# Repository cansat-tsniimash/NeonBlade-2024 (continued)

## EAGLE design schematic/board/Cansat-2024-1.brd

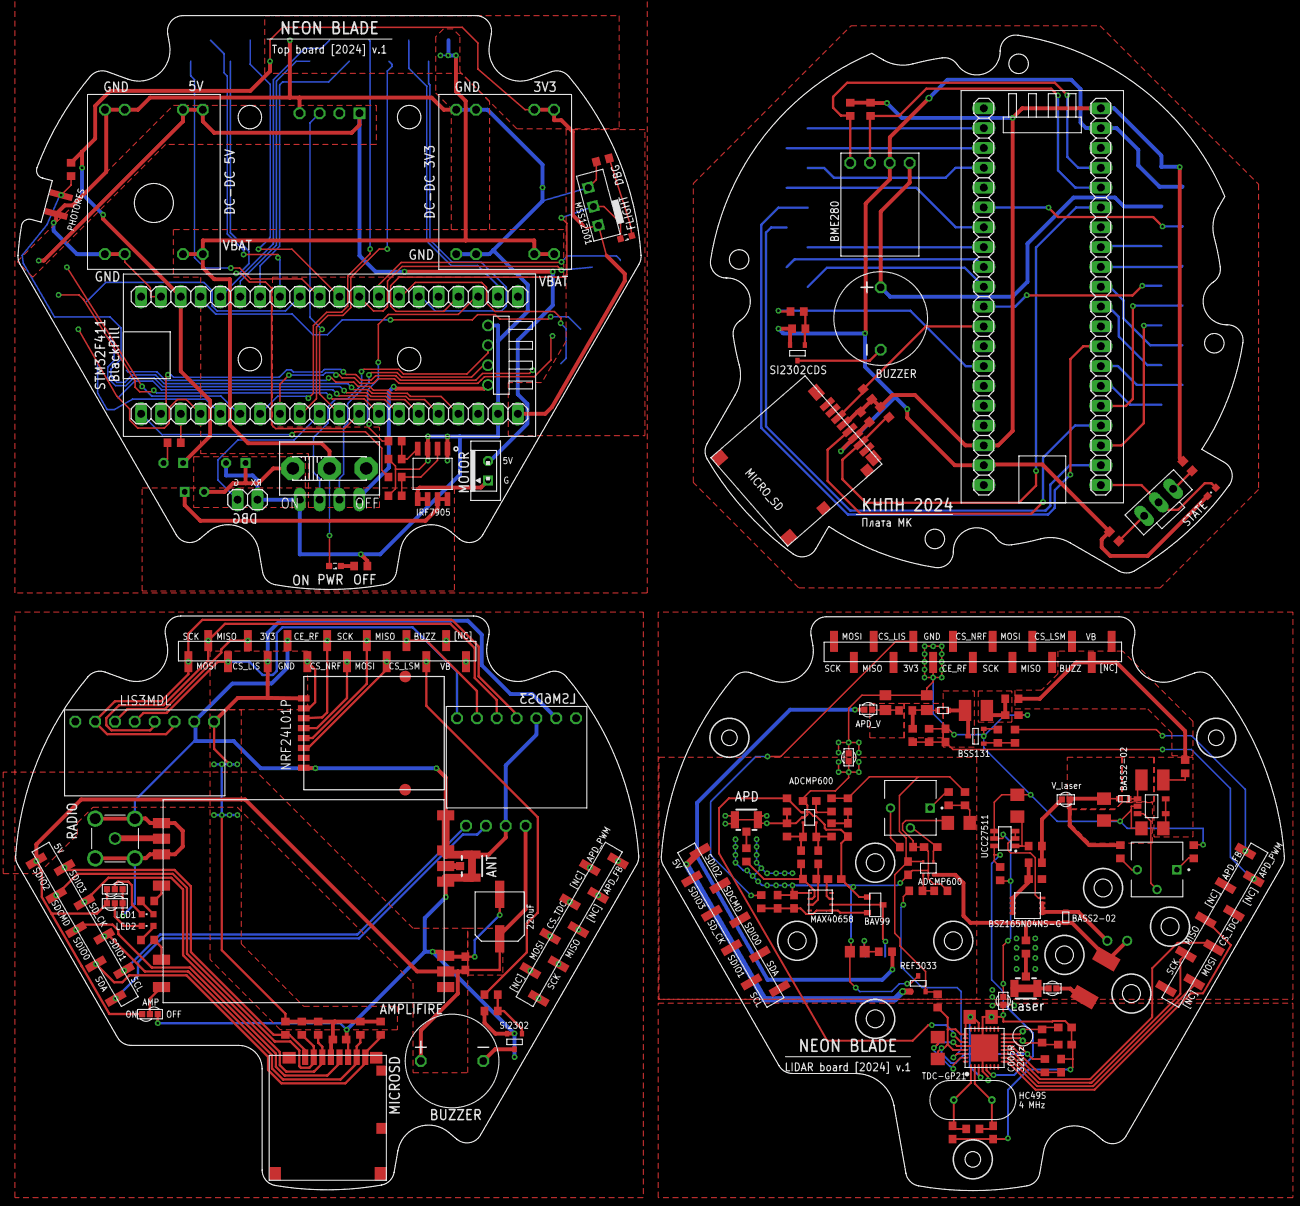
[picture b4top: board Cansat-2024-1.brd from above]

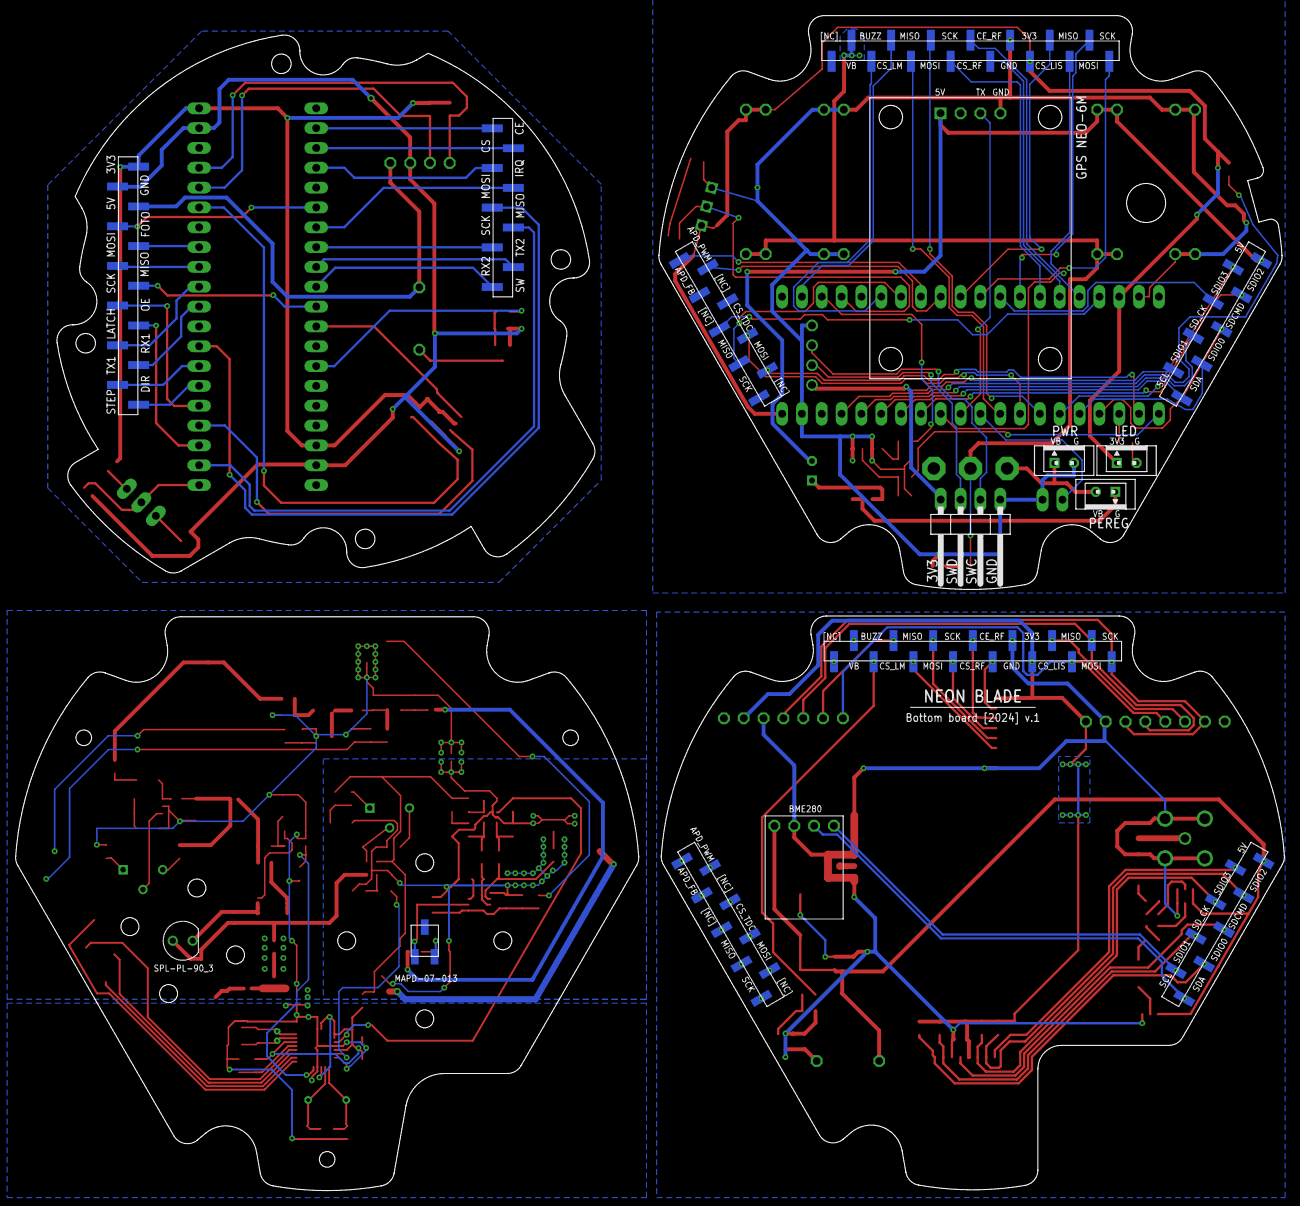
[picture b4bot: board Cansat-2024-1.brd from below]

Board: 2 copper layers, 162.5 x 150.5 mm, 169 parts (17 on the bottom side), 182 nets.

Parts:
AMPLIFIRE: XQ-02A
ANT: U.FL-R-SMT-1_10_; U.FL-R-SMT-1(10)
BME280: BME280BME280-PINS-ONLY; BME280-PINS-ONLY
BUZZER, BUZZER1: BUZZERS8R6; BUZZER-S8R12
C1, C7, C12, C23, C24, C27, C28, C29: 100nF; C0603
C2, C3: 15pF; C0603
C4, C9, C16, C19: 10uF; C1206
C5: 10nF 250v; C0805
C6, C13, C14, C26: 1uF; C0603
C8: 100pF; C0603
C10: 220uF; ECAP220-CMD
C11, C33: 10nF 250V; C0805
C15, C25: 10nF; C0603
C17: 22nF low ESR; C0603
C18, C20: 22uF; C1206
C21, C22: 10pF; C0603
D1: BAS521; SOD523
D2: BAS52-02; SOD523
D6: BAV99
DC-DC_3V3, DC-DC_5V: MP1584-B
J1, J2: U.FL-R-SMT-1_10_; U.FL-R-SMT-1(10)
JP1: 1X04/90
JP2: 1X02
L1, L2, L4, L6, L7, L8, L9, L10: L_BEAD
L3: 10uH; L_1210
L5: 47uH; 1210
LED1, LED2: CHIPLED_0603
LED7, LED8: SML0603
LIS3MDL: LIS3MDL-CJMCUбез_отв.; LIS3MDL-CGMSU-NB2023-1
LSM6DS3: LSM6DS3-GY-NB2023
MICROSD: SD
MICRO_SD: SD
NRF24L01P: NRF24L01_ML01SP4
PHOTORES: PHOTORES_VT93N1; PHOTORES_VT93N1_SMD
R1, R3, R4, R6, R17, R45, R46: 2k; R0603
R2, R7, R8, R9, R10: 3k3; R0603
R5: 5K1; R0603
R11, R12, R31, R43, R49, R50: 10k; R0603
R13, R14: 100; R0603
R15, R19, R25, R32, R41: 4.7k; R0603
R16: 560k; R0603
R18, R20: 47k; R0603
R21, R30, R44: 100R; R0603
R22: 2M; R0603
R23: 20k; R0603
R24: 10M; R0603
R26, R35, R38, R39: 1k; R0603
R27: 270; R0603
R28: R100; R2512
R29, R37: 47R; R0603
R33: 100k; R0603
R34: 0R; R0603
R36: NC; R0603
R40: 150R; R0603
R42: 4k7; R0603
R47, R48: 5k1; R0603
RADIO: MCX-J-P-H-ST-TH1; MCXJPHSTTH1
REF3033: REF3033; SOT23-3
S2: UNICS-SWITCH
SI2302: MOSFET-N; SOT23-3
SI2302CDS: SI2302CDS; SOT23-3
STATE: CHIPLED_0603
STM: STM32F411_BOARD
U$1: BME280BME280-PINS-ONLY; BME280-PINS-ONLY
U$2, U$3, U$6, U$7, U$13, U$14, U$23, U$24, U$38: PBS_SMD_X9
U$4, U$8, U$15, U$25: PBS_SMD_X15; PBD_SMD_X15
U$5, U$9, U$10: VIAS-SELECT
U$11: STM32F401_BOARD
U$12: MSS12D01
U$16: GPS_NEO6M; GPS_NEO6M_NEW
U$17: IRF7905PBF; SO8
U$18: TDC-GP21
U$19: C005R
U$20: HC49S
U$21: MIC2288
U$22: BSS131; SOT23-3
U$26: UCC27511DBVR
U$27: BSZ165N04NS-G
U$28: BAS52-02; SOD523
U$29: SPL_PL-90
U$30, U$32: ADCMP600
U$31: MAX40658-8-TDFN-3X3MM
U$33: MTAPD-07-013; MAPD-07-013
U$34, U$35: VIAS-CONNECT
U$36: SWITCH_MSS
U$37: PBS_SMD_X13; PBD_SMD_X13
U$39: Плата МК; LOGO
VR1, VR2: 3362P-1-502LF; TRIM_3362P-1-502LF
W1, W3, W5: VIAS-CONNECT
X1, X2, X3, X4: JST-2-K-S; B2B-PH-K-S

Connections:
1MISO: LIS3MDL.P$5, LSM6DS3.P$1, U$4.3, U$8.13
1MISO1: U$11.32, U$15.3
1MOSI: LIS3MDL.P$4, LSM6DS3.P$3, U$4.2, U$8.14
1MOSI1: U$11.13, U$15.2
1SCK: LIS3MDL.P$3, LSM6DS3.P$4, U$4.1, U$8.15
1SCK1: U$11.11, U$15.1
3V1: DC-DC_3V3.P$7, DC-DC_3V3.P$8, R17.1, U$11.18, U$11.40, U$12.P$2, U$15.5, X2.1
3V2: L1.1, U$25.5
3V3: C7.2, LIS3MDL.P$1, LSM6DS3.P$6, MICROSD.VDD, NRF24L01P.P$1, R2.2, R7.2, R8.2, R9.2, R10.2, U$4.5, U$8.11
3V3_REF: C24.1, L6.1, L7.1, L9.2, L10.1, REF3033.2, U$30.P$5
3V4: C28.2, MICRO_SD.VDD, R46.2, R47.2, R48.2, R49.1, R50.1, STM.18, STM.40, U$37.1
4MISO: U$11.28, U$13.4
4MISO1: U$18.12, U$23.4
4MOSI: U$11.7, U$13.3
4MOSI1: U$18.11, U$23.3
4SCK: U$11.22, U$13.2
4SCK1: U$18.10, U$23.2
5MISO: NRF24L01P.P$6, U$4.11, U$8.5
5MISO1: U$11.29, U$15.11
5MOSI: NRF24L01P.P$5, U$4.10, U$8.6
5MOSI1: U$11.27, U$15.10
5SCK: NRF24L01P.P$4, U$4.9, U$8.7
5SCK1: U$11.14, U$15.9
5V: AMPLIFIRE.P$5, BUZZER.P$1, C1.2, C10.P$1, U$1.P$1, U$2.9, U$5.3, U$6.1, U$9.3, U$10.3
5V1: DC-DC_5V.P$7, DC-DC_5V.P$8, U$14.1, U$16.P$1, X3.2
5V2: REF3033.1, U$24.1
5V3: BME280.P$4, BUZZER1.P$2, U$37.3
ADC_FOTO: STM.6, U$37.4
AGND: C12.2, C13.2, C14.2, C19.1, C23.2, C24.2, C26.1, C27.1, C33.2, D6.P$1, J1.1, J1.2, R32.1, R35.1, R39.1, R42.2, REF3033.3, U$30.P$2, U$31.P$5, U$32.P$2, W5.1
APD_COMP_OUT: R39.2, U$18.27, U$32.P$1
APD_FB_VOLT: U$11.9, U$13.8
APD_FB_VOLT1: C8.2, R22.1, R23.2, U$23.8
APD_PWM: U$11.8, U$13.9
APD_PWM1: R21.2, U$23.9
APD_V: C11.2, R25.1, U$34.1
APD_V_: R38.2, U$34.2
BUZZER: R30.1, U$4.13, U$8.3
BUZZER1: U$11.6, U$15.13
BUZZER2: R44.1, STM.14
CE_NRF: NRF24L01P.P$2, U$4.7, U$8.9
CE_NRF1: U$11.15, U$15.7
CE_RADIO: STM.2, U$38.9
CMD_SD: MICRO_SD.CMD, R50.2, STM.12
COMP_N: C15.2, R40.1, R41.2, U$32.P$4
COMP_P: C25.2, R40.2, R42.1, U$32.P$3
CS_LIS: LIS3MDL.P$6, U$4.4, U$8.12
CS_LIS1: U$11.10, U$15.4
CS_LSM: LSM6DS3.P$2, U$4.12, U$8.4
CS_LSM1: U$11.2, U$15.12
CS_NRF: NRF24L01P.P$3, U$4.8, U$8.8
CS_NRF1: U$11.16, U$15.8
CS_RADIO: STM.3, U$38.8
CS_TDC: U$11.17, U$13.5
CS_TDC1: U$18.9, U$23.5
D0_SD: MICRO_SD.DAT0, R49.2, STM.35
DBG_3V3: JP1.4, U$11.3V3
DBG_TX: JP2.1, U$11.30
DIR_DRIVER: STM.27, U$37.12
DRUGATEL: R14.1, U$11.3
GND: AMPLIFIRE.P$1, AMPLIFIRE.P$2, AMPLIFIRE.P$4, AMPLIFIRE.P$10, AMPLIFIRE.P$12, AMPLIFIRE.P$13, ANT.1, ANT.2, C1.1, C7.1, C10.P$2, LIS3MDL.P$2, LSM6DS3.P$5, MICROSD.VSS, NRF24L01P.P$8, R31.2, RADIO.2, RADIO.3, RADIO.4, RADIO.5, SI2302.2, U$1.P$2, U$4.6, U$5.1, U$8.10, U$9.1, U$10.1
GND1: DC-DC_3V3.P$3, DC-DC_3V3.P$4, DC-DC_3V3.P$5, DC-DC_3V3.P$6, DC-DC_5V.P$3, DC-DC_5V.P$4, DC-DC_5V.P$5, DC-DC_5V.P$6, JP1.1, JP2.2, PHOTORES.P$1, R4.2, R5.2, R11.1, R12.2, U$11.19, U$11.39, U$11.GND, U$12.P$3, U$15.6, U$16.P$4, U$17.1, U$17.3, X1.2
GND2: C2.1, C3.1, C18.1, C20.1, C21.1, C22.1, C29.2, U$18.4, U$18.21, U$18.28, U$18.31, U$18.P$1, W1.2
GND3: BME280.P$3, C28.1, MICRO_SD.VSS, R43.2, R45.2, SI2302CDS.2, STATE.C, STM.19, STM.39, U$37.2
GPS_RX: U$11.31, U$16.P$3
IRQ_RADIO: STM.4, U$38.7
I_LASER: R28.2, R29.2, U$28.P$2, U$29.P$2, U$30.P$3
LASER_COMP: R34.1, U$18.30
LASER_PULSE: R26.2, U$18.5, U$26.P$6
LATCH_SR: STM.23, U$37.9
LED: R6.1, U$11.23
MISO_RADIO: STM.28, U$38.5
MISO_SR: STM.32, U$37.6
MOSI_RADIO: STM.7, U$38.6
MOSI_SR: STM.33, U$37.5
unnamed: R30.2, R31.1, SI2302.1
unnamed: U$4.14, U$8.2
unnamed: U$4.15, U$8.1
unnamed: AMPLIFIRE.P$3, ANT.3
unnamed: AMPLIFIRE.P$11, RADIO.1
unnamed: U$3.8, U$7.2
unnamed: U$3.7, U$7.3
unnamed: U$3.6, U$7.4
unnamed: U$3.5, U$7.5
unnamed: U$3.4, U$7.6
unnamed: U$3.3, U$7.7
unnamed: U$3.9, U$7.1
unnamed: LED8.C, R4.1
unnamed: U$3.2, U$7.8
unnamed: U$3.1, U$7.9
unnamed: LED1.C, U$5.2
unnamed: LED1.A, R1.2
unnamed: AMPLIFIRE.P$8, R1.1
unnamed: LED2.C, U$9.2
unnamed: BUZZER.P$2, SI2302.3
unnamed: LED2.A, R3.2
unnamed: AMPLIFIRE.P$9, R3.1
unnamed: S2.1, X1.1, X4.2
unnamed: LED7.C, R5.1
unnamed: U$17.5, U$17.6, X3.1
unnamed: U$17.7, U$17.8, X4.1
unnamed: R12.1, R14.2, U$17.4
unnamed: R11.2, R13.2, U$17.2
unnamed: R6.2, X2.2
unnamed: C29.1, R15.1, U$18.13
unnamed: C21.2, R24.2, U$18.15, U$19.P$2
unnamed: C22.2, R24.1, U$18.16, U$19.P$1
unnamed: C2.2, R16.1, U$18.2, U$20.P$1
unnamed: C3.2, R16.2, U$18.1, U$20.P$2
unnamed: C4.2, L2.1, L3.1, U$21.EN, U$21.VIN
unnamed: D2.P$2, L3.2, U$21.SW
unnamed: U$21.FB, VR1.2
unnamed: R19.1, VR1.1
unnamed: R18.2, VR1.3
unnamed: R20.2, R21.1, U$22.1
unnamed: D1.P$2, L5.2, U$22.3
unnamed: C5.2, D1.P$1, R22.2, R25.2
unnamed: C6.1, L4.2, L5.1
unnamed: U$26.P$2, U$26.P$3, U$27.P$4
unnamed: C16.1, L8.2, U$26.P$1
unnamed: C17.2, R27.1, U$27.P$5, U$27.P$6, U$27.P$7, U$27.P$8
unnamed: U$27.P$1, U$27.P$2, U$27.P$3, U$28.P$1, U$29.P$1
unnamed: J2.3, R29.1
unnamed: J2.1, J2.2, W3.2
unnamed: C23.1, U$30.P$4, VR2.2
unnamed: C19.2, L10.2, R33.2
unnamed: R34.2, R35.2, U$30.P$1
unnamed: R33.1, VR2.1
unnamed: R32.2, VR2.3
unnamed: D6.P$3, U$31.P$2, U$33.P$2
unnamed: C14.1, U$31.P$3
unnamed: C15.1, R36.2, U$31.P$7
unnamed: C25.1, R36.1, R37.2, U$31.P$6
unnamed: J1.3, R37.1
unnamed: C33.1, R38.1, U$33.P$3
unnamed: C26.2, L6.2, R41.1
unnamed: C27.2, L7.2, U$32.P$5
unnamed: BUZZER1.P$1, SI2302CDS.3
unnamed: R43.1, R44.2, SI2302CDS.1
unnamed: R45.1, U$36.3
unnamed: R46.1, U$36.1
OE_SR: STM.25, U$37.8
PERESHIGATEL: R13.1, U$11.21
PGND: C4.1, C5.1, C6.2, C8.1, C9.1, C11.1, C16.2, C17.1, R19.2, R20.1, R23.1, R26.1, R28.1, U$21.GND, U$22.2, U$25.6, U$26.P$4, U$26.P$5, W1.1, W3.1, W5.2
PHOTORES: PHOTORES.P$2, R17.2, U$11.36
RX1_BLE: STM.31, U$37.10
RX2_GPS: STM.9, U$38.2
SCK_RADIO: STM.22, U$38.4
SCK_SR: STM.11, U$37.7
SCL: U$1.P$3, U$2.1, U$6.9
SCL1: U$11.34, U$14.9
SCL2: BME280.P$2, R48.1, STM.36
SDA: U$1.P$4, U$2.2, U$6.8
SDA1: U$11.37, U$14.8
SDA2: BME280.P$1, R47.1, STM.37
SDIO_CK: MICROSD.CLK, U$2.5, U$6.5
SDIO_CK1: U$11.24, U$14.5
SDIO_CMD: MICROSD.CMD, R8.1, U$2.6, U$6.4
SDIO_CMD1: U$11.12, U$14.4
SDIO_DAT0: MICROSD.DAT0, R9.1, U$2.4, U$6.6
SDIO_DAT1: MICROSD.DAT1, R10.1, U$2.3, U$6.7
SDIO_DAT2: MICROSD.DAT2, R2.1, U$2.8, U$6.2
SDIO_DAT3: MICROSD.DAT3, R7.1, U$2.7, U$6.3
SDIO_DAT4: U$11.26, U$14.2
SDIO_DAT5: U$11.33, U$14.3
SDIO_DAT6: U$11.35, U$14.6
SDIO_DAT7: U$11.25, U$14.7
SD_CK: MICRO_SD.CLK, STM.24
STATE: LED8.A, U$11.4, U$12.P$1
STEP_DRIVER: STM.26, U$37.13
SWC: JP1.2, U$11.SWC
SWD: JP1.3, U$11.SWD
SWITCH: STATE.A, STM.21, U$36.2
SW_AMP: STM.10, U$38.1
TX1_BLE: STM.30, U$37.11
TX2_GPS: STM.8, U$38.3
USIL_ON: AMPLIFIRE.P$7, U$10.2
VCC_TIA: C12.1, C13.1, D6.P$2, L1.2, U$31.P$1
VLASER: C9.2, D2.P$1, R18.1, U$35.1
VLASER_: L8.1, R27.2, U$35.2
V_BAT: DC-DC_3V3.P$1, DC-DC_3V3.P$2, DC-DC_5V.P$1, DC-DC_5V.P$2, LED7.A, S2.2, U$15.14
V_BAT1: L2.2, L4.1, U$25.14
V_TDC: C18.2, C20.2, L9.1, R15.2, U$18.3, U$18.14, U$18.22, U$18.25, U$18.26, U$18.29

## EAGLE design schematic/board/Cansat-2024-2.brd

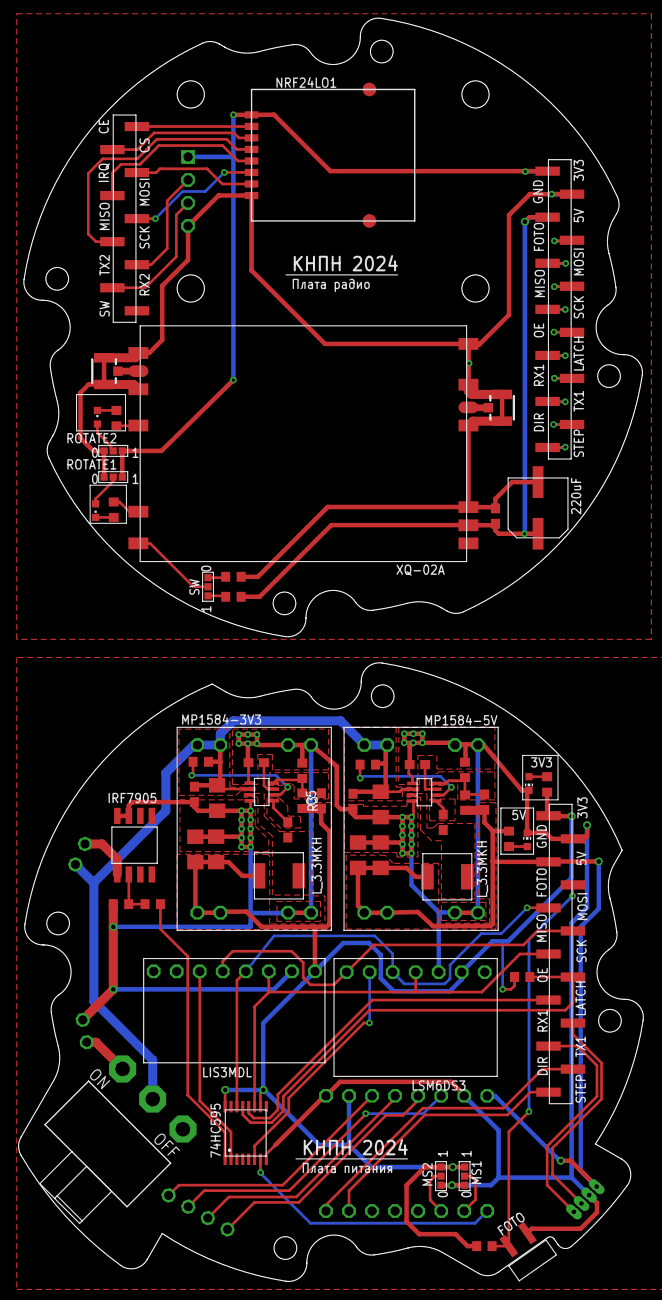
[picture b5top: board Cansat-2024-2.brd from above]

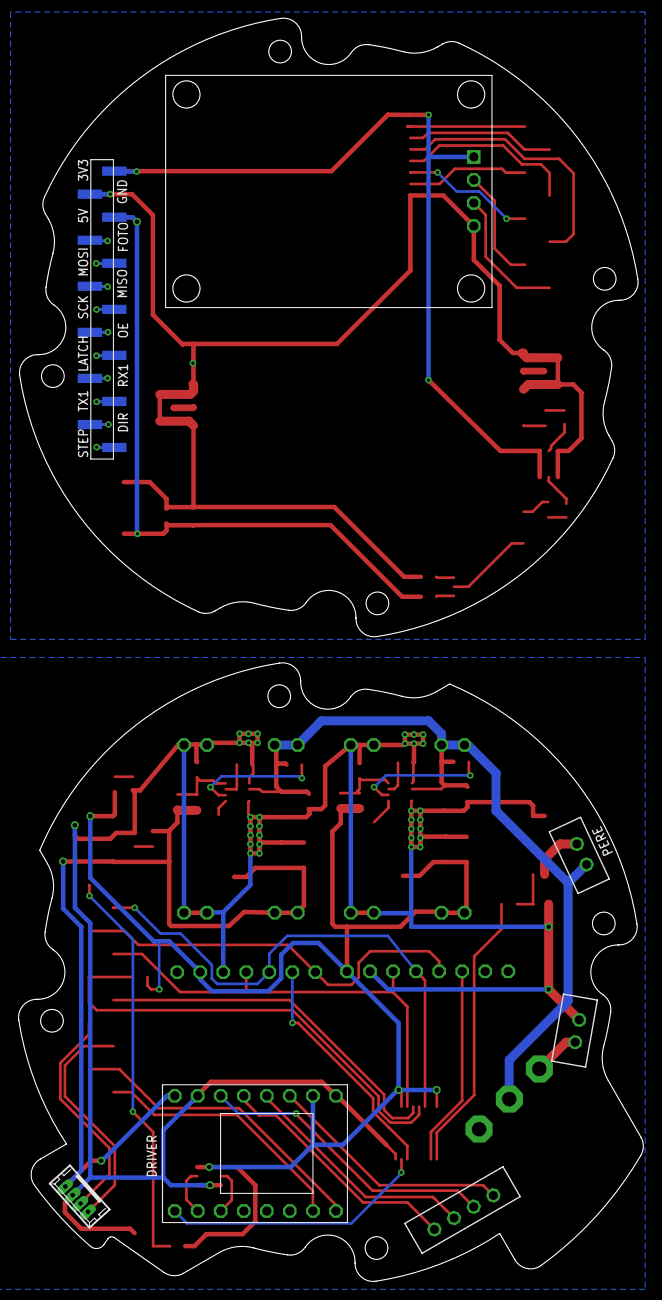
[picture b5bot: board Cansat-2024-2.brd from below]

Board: 2 copper layers, 68.9 x 139.3 mm, 69 parts (7 on the bottom side), 71 nets.

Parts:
3V3, 5V: CHIP-LED0603
74HC595: 74HC595; TSSOP16
C1, C4, C8, C11: 0,1u; C0603
C2, C9: 0,1u; C1206
C3, C10: 22u; C0603
C5, C12: 33p; C0603
C6, C7, C13, C14: 22u; C1206
C15: 100nF; C0603
C16: 220uF; ECAP220-CMD
DRIVER: TMC2209_WITHOUT
FOTO: VT93N1
GPS-NEO7M: GPS-NEO7M
IRF7905: IRF7905PBF; SO8
J1: IPX-RADIO; U.FL-R-SMT-1(10)
J2: IPX-ANT; U.FL-R-SMT-1(10)
LED1: AMP1; CHIPLED_0603
LED2: AMP2; CHIPLED_0603
LIS3MDL: LIS3MDL
LSM6DS3: LSM6DS3_WITHOUT
L_3.3: L_3.3MKH; L_SPM5020
MP1584-3V3: MP1584-B
MP1584-5V: MP1584; MP1584-B
MS1, MS2: CONNECT_3
NRF24LO1: NRF24L01_ML01SP4
R1, R4: 100k; R0603
R2, R5, R8, R10: 10k; R0603
R3: 31k6; R0603
R6: 53k6; R0603
R7, R11, R12, R13, R14, R15, R16: 2k; R0603
R9: 100R; R0603
ROTATE1, ROTATE2: CONNECT_3
S1: SS_12D11
SW: CONNECT_3
U$1: Плата питания; LOGO
U$2, U$5: MP2225; TSOT23-8
U$3, U$8, U$10: PBS_SMD_X13; PBD_SMD_X13
U$4: Плата радио; LOGO
U$6: L_3.3MKH; L_SPM5020
U$7: PBS_SMD_X9
U$9: STEP_MOT; JST-4-2.5
U$14: BLUETOOTH; 53047-04
X1: PERE; JST-2-2.5
X2: AKKUM; JST-2-2.5
XQ-02A: XQ-02A

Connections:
3V1: GPS-NEO7M.P$1, NRF24LO1.P$1, ROTATE1.1, ROTATE2.1, U$3.13, U$8.1
3V3: 74HC595.10, 74HC595.16, C5.1, C6.2, C7.2, DRIVER.P10, LIS3MDL.UCC, LSM6DS3.P$2, L_3.3.P$1, MP1584-3V3.P$7, MP1584-3V3.P$8, MS1.1, MS2.1, R3.2, R7.1, R8.2, R12.2, U$10.13
5V: C12.1, C13.2, C14.2, DRIVER.P$16, MP1584-5V.P$7, MP1584-5V.P$8, R6.2, R11.2, U$6.P$1, U$10.11, U$14.1
5V1: C15.2, C16.P$1, R15.1, U$3.11, U$8.3, XQ-02A.5V
A1: DRIVER.P$13, U$9.1
A2: DRIVER.P$14, U$9.3
ADC_FOTO: U$3.10, U$8.4
ANT_RADIO: J2.3, XQ-02A.ANT
B1: DRIVER.P$12, U$9.2
B2: DRIVER.P$11, U$9.4
BUS+: C2.2, C3.2, C9.2, C10.2, MP1584-3V3.P$1, MP1584-3V3.P$2, MP1584-5V.P$1, MP1584-5V.P$2, R1.1, R4.1, S1.2, U$2.P$2, U$5.P$2, X1.1
BUS+_OUT: S1.3, X2.1
CE_RADIO: NRF24LO1.P$2, U$7.1
CS_LIS: 74HC595.2, LIS3MDL.CS
CS_LSM: 74HC595.6, LSM6DS3.P$6
CS_RADIO: NRF24LO1.P$3, U$7.2
DIR_DRIVER: DRIVER.P$1, U$10.2
DIR_DRIVER1: U$3.2, U$8.12
EN_DRIVER: 74HC595.7, DRIVER.P$8
FOTO: FOTO.P$2, R7.2, U$10.10
GND: 3V3.C, 5V.C, 74HC595.8, C1.1, C2.1, C3.1, C6.1, C7.1, C8.1, C9.1, C10.1, C13.1, C14.1, DRIVER.P$9, DRIVER.P$15, FOTO.P$1, IRF7905.7, IRF7905.8, LIS3MDL.GND, LSM6DS3.P$3, MP1584-3V3.P$3, MP1584-3V3.P$4, MP1584-3V3.P$5, MP1584-3V3.P$6, MP1584-5V.P$3, MP1584-5V.P$4, MP1584-5V.P$5, MP1584-5V.P$6, MS1.3, MS2.3, R2.2, R5.2, R10.1, U$2.P$1, U$2.P$4, U$5.P$1, U$5.P$4, U$10.12, U$14.2, X2.2
GND1: C15.1, C16.P$2, GPS-NEO7M.P$4, J1.1, J1.2, J2.1, J2.2, NRF24LO1.P$8, R16.1, ROTATE1.3, ROTATE2.3, U$3.12, U$8.2, XQ-02A.GND, XQ-02A.GND1, XQ-02A.GND2, XQ-02A.GND3, XQ-02A.GND4, XQ-02A.GND5
IRQ_RADIO: NRF24LO1.P$7, U$7.3
LATCH_SR: 74HC595.12, U$10.5
LATCH_SR1: U$3.5, U$8.9
MISO_RADIO: NRF24LO1.P$6, U$7.5
MISO_SR: LIS3MDL.SDO, LSM6DS3.P$7, U$10.8
MISO_SR1: U$3.8, U$8.6
MOSI_RADIO: NRF24LO1.P$5, U$7.4
MOSI_SR: 74HC595.14, LIS3MDL.SDA, LSM6DS3.P$5, U$10.9
MOSI_SR1: U$3.9, U$8.5
MS1: DRIVER.P$7, MS1.2
MS2: DRIVER.P$6, MS2.2
unnamed: C1.2, U$2.P$7
unnamed: R1.2, U$2.P$6
unnamed: C4.2, U$2.P$5
unnamed: C4.1, L_3.3.P$2, U$2.P$3
unnamed: C5.2, R2.1, R3.1, U$2.P$8
unnamed: IRF7905.2, R9.1, R10.2
unnamed: C8.2, U$5.P$7
unnamed: R4.2, U$5.P$6
unnamed: C11.2, U$5.P$5
unnamed: C11.1, U$5.P$3, U$6.P$2
unnamed: C12.2, R5.1, R6.1, U$5.P$8
unnamed: 5V.A, R11.1
unnamed: 3V3.A, R12.1
unnamed: LED1.C, R13.2
unnamed: LED2.C, R14.2
unnamed: LED1.A, ROTATE1.2
unnamed: LED2.A, ROTATE2.2
unnamed: R14.1, XQ-02A.LED2
unnamed: R13.1, XQ-02A.LED1
unnamed: R15.2, SW.1
unnamed: R16.2, SW.3
OE_SR: 74HC595.13, R8.1, U$10.6
OE_SR1: U$3.6, U$8.8
PERE: 74HC595.1, R9.2
PERE_G: IRF7905.1, X1.2
RF-IN: J1.3, XQ-02A.RF-IN
RX1_BLE: U$10.4, U$14.3
RX1_BLE1: U$3.4, U$8.10
RX2_GPS: GPS-NEO7M.P$3, U$7.8
SCK_RADIO: NRF24LO1.P$4, U$7.6
SCK_SR: 74HC595.11, LIS3MDL.SCL, LSM6DS3.P$4, U$10.7
SCK_SR1: U$3.7, U$8.7
STEP_DRIVER: DRIVER.P$2, U$10.1
STEP_DRIVER1: U$3.1, U$8.13
SW: SW.2, XQ-02A.SW
TX1_BLE: U$10.3, U$14.4
TX1_BLE1: U$3.3, U$8.11
TX2_GPS: GPS-NEO7M.P$2, U$7.7

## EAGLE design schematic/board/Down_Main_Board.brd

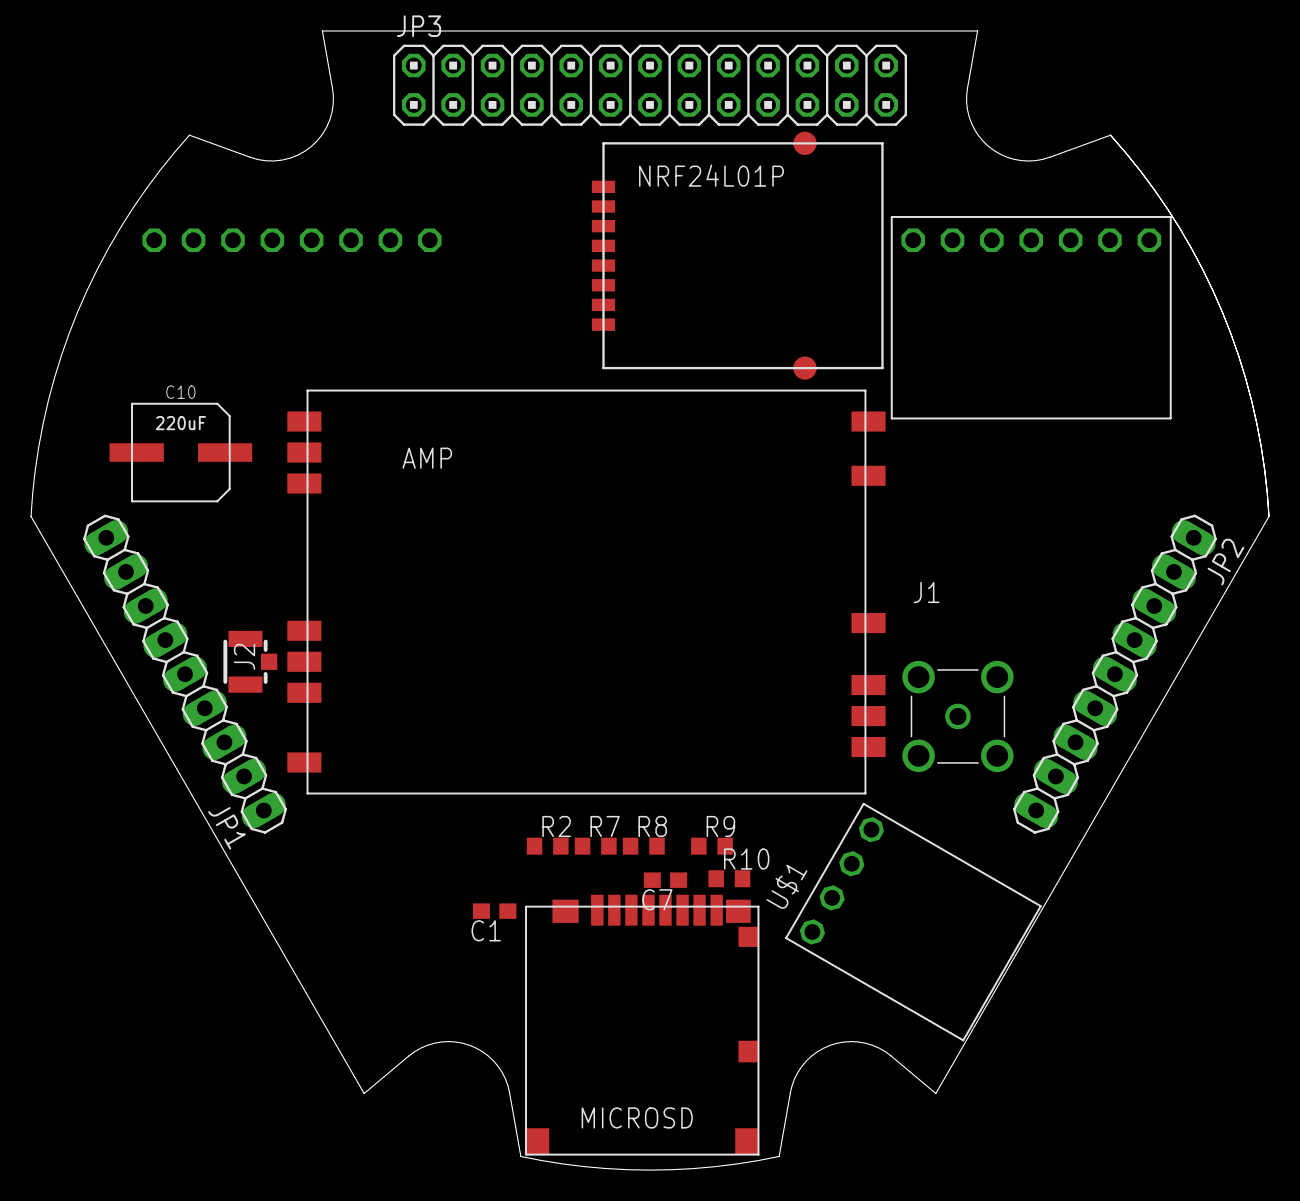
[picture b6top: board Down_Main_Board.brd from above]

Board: 2 copper layers, 79.9 x 73.5 mm, 19 parts (1 on the bottom side), 13 nets, no tracks yet.

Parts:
AMP: XQ-02A
C1, C7: 100nF; C0603
C10: 220uF; ECAP220-CMD
J1: MCX-J-P-H-ST-TH1; MCXJPHSTTH1
J2: U.FL-R-SMT-1_10_; U.FL-R-SMT-1(10)
JP1, JP2: 1X09
JP3: 2X13
LIS3MDL: LIS3MDL-CJMCUБез_отв._зеркальный; LIS3MDL-CGMSU-NB2023
LSM6DS3: LSM6DS3-GY-NB2023
MICROSD: SD
NRF24L01P: NRF24L01_ML01SP4
R2, R7, R8, R9, R10: 3k3; R0603
U$1: BME280BME280-PINS-ONLY; BME280-PINS-ONLY

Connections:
3V3: C7.2, LIS3MDL.P$1, LSM6DS3.P$6, MICROSD.VDD, NRF24L01P.P$1, R2.2, R7.2, R8.2, R9.2, R10.2
5V: AMP.P$5, C1.2, C10.P$1
GND: AMP.P$1, AMP.P$2, AMP.P$4, AMP.P$10, AMP.P$12, AMP.P$13, C1.1, C7.1, C10.P$2, J1.2, J1.3, J1.4, J1.5, J2.1, J2.2, LIS3MDL.P$2, LSM6DS3.P$5, MICROSD.VSS, NRF24L01P.P$8
MISO: LIS3MDL.P$5, LSM6DS3.P$1, NRF24L01P.P$6
MOSI: LIS3MDL.P$4, LSM6DS3.P$3, NRF24L01P.P$5
unnamed: AMP.P$3, J2.3
unnamed: AMP.P$11, J1.1
SCK: LIS3MDL.P$3, LSM6DS3.P$4, NRF24L01P.P$4
SDIO_CMD: MICROSD.CMD, R8.1
SDIO_DAT0: MICROSD.DAT0, R9.1
SDIO_DAT1: MICROSD.DAT1, R10.1
SDIO_DAT2: MICROSD.DAT2, R2.1
SDIO_DAT3: MICROSD.DAT3, R7.1

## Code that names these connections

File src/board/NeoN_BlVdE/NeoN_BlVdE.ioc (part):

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Mcu.Name=STM32F411C(C-E)Ux
Mcu.Package=UFQFPN48
Mcu.UserName=STM32F411CEUx
PA0-WKUP.Signal=ADCx_IN0
PA1.Mode=Full_Duplex_Master
PA1.Signal=SPI4_MOSI
PA10.Mode=Full_Duplex_Master
PA10.Signal=SPI5_MOSI
PA11.Mode=Full_Duplex_Master
PA11.Signal=SPI4_MISO
PA12.Mode=Full_Duplex_Master
PA12.Signal=SPI5_MISO
PA13.Mode=Serial_Wire
PA13.Signal=SYS_JTMS-SWDIO
PA14.Mode=Serial_Wire
PA14.Signal=SYS_JTCK-SWCLK
PA15.Mode=Asynchronous
PA15.Signal=USART1_TX
PA2.Signal=S_TIM5_CH3
PA3.GPIOParameters=GPIO_Label
PA3.GPIO_Label=APD_FB_VOLT
PA3.Signal=ADCx_IN3
PA4.GPIOParameters=PinState,GPIO_Label
PA4.GPIO_Label=LIS_CS
PA4.PinState=GPIO_PIN_SET
PA4.Signal=GPIO_Output
PA5.Mode=Full_Duplex_Master
PA5.Signal=SPI1_SCK
PA6.GPIOParameters=GPIO_PuPd,GPIO_Speed_High_Default,GPIO_Mode
PA6.GPIO_Mode=GPIO_MODE_AF_PP
PA6.GPIO_PuPd=GPIO_NOPULL
PA6.GPIO_Speed_High_Default=GPIO_SPEED_FREQ_VERY_HIGH
PA6.Mode=SD_1_bit
PA6.Signal=SDIO_CMD
PA7.Mode=Full_Duplex_Master
PA7.Signal=SPI1_MOSI
PA8.Signal=SDIO_D1
PA9.Signal=SDIO_D2
PB0.Mode=Full_Duplex_Master
PB0.Signal=SPI5_SCK
PB1.GPIOParameters=GPIO_Label
PB1.GPIO_Label=NRF_CE
PB1.Signal=GPIO_Output
PB10.GPIOParameters=GPIO_Label
PB10.GPIO_Label=CS_TDC
PB10.Signal=GPIO_Output
PB12.GPIOParameters=GPIO_Label
PB12.GPIO_Label=PEREGIGATEL
PB12.Signal=GPIO_Output
PB13.Mode=Full_Duplex_Master
PB13.Signal=SPI4_SCK
PB14.GPIOParameters=GPIO_Label
PB14.GPIO_Label=LED
PB14.Signal=GPIO_Output
PB15.GPIOParameters=GPIO_PuPd,GPIO_Speed_High_Default,GPIO_Mode
PB15.GPIO_Mode=GPIO_MODE_AF_PP
PB15.GPIO_PuPd=GPIO_NOPULL
PB15.GPIO_Speed_High_Default=GPIO_SPEED_FREQ_VERY_HIGH
PB15.Mode=SD_1_bit
PB15.Signal=SDIO_CK
PB2.GPIOParameters=GPIO_Label
PB2.GPIO_Label=NRF_CS
PB2.Signal=GPIO_Output
PB3.Mode=Asynchronous
PB3.Signal=USART1_RX
PB4.Mode=Full_Duplex_Master
PB4.Signal=SPI1_MISO
PB5.Signal=SDIO_D3
PB6.Mode=I2C
PB6.Signal=I2C1_SCL
PB7.Mode=SD_1_bit
PB7.Signal=SDIO_D0
PB8.GPIOParameters=GPIO_Label
PB8.GPIO_Label=BUZZER
PB8.Signal=GPIO_Output
PB9.Mode=I2C
PB9.Signal=I2C1_SDA
PC13-ANTI_TAMP.GPIOParameters=PinState,GPIO_Label
PC13-ANTI_TAMP.GPIO_Label=LSM_CS
PC13-ANTI_TAMP.PinState=GPIO_PIN_SET
PC13-ANTI_TAMP.Signal=GPIO_Output
PC14-OSC32_IN.GPIOParameters=GPIO_Label
PC14-OSC32_IN.GPIO_Label=MOTOR
PC14-OSC32_IN.Signal=GPIO_Output
PC15-OSC32_OUT.GPIOParameters=GPIO_Label
PC15-OSC32_OUT.GPIO_Label=STATE
PC15-OSC32_OUT.Signal=GPIO_Input
PH0\ -\ OSC_IN.GPIOParameters=GPIO_Label
PH0\ -\ OSC_IN.GPIO_Label=TDC_INT
PH0\ -\ OSC_IN.Signal=GPIO_Input
RCC.HSE_VALUE=25000000
RCC.SYSCLKFreq_VALUE=100000000
RCC.SYSCLKSource=RCC_SYSCLKSOURCE_PLLCLK
board=custom

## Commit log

2023-11-04 поправил
2023-11-24 Создал папочки в репозитории
2023-11-25 Удалил временно файл
2023-11-25 Вернул файл
2023-11-25 Сборка нижнего модуля.
2023-11-25 Сборка нижнего модуля. (поправил)
2023-11-29 Добавил вырезы на плате. Исправил версии моделей
2023-11-29 Модели плат
2023-11-29 Модели плат(очистил старые версии)
2023-11-29 в 100500 раз поменял плату
2023-12-01 Пишем драйвер TDC-GP21. Определили регистры и команды
2023-12-01 100501 раз изменил пины на плате
2023-12-01 Сборка нижнего модуля с платами
2023-12-02 Развод на плате...
2023-12-02 поменял гпс на верхней плате
2023-12-13 какая то плата
2023-12-15 спонсор страданий
2023-12-15 Down_плата
2023-12-16 переделал плату лидара
2023-12-16 добавил элементы стабилизации
2023-12-16 Добавил гитигнор в scematic
2023-12-17 я сделял
2023-12-22 немного переделал плату лидара
2023-12-22 ага угу
2023-12-23 Безумие — это точное повторение одного и того же действия раз за разом в надежде на изменение
2023-12-23 Даниил на протяжении 510 лет переделывает плату лидара
2023-12-29 внес изменения в модель аппарата
2023-12-29 почти добавил новый разъём
2024-01-03 Добавил в папку с аппаратом потерявшиеся модели
2024-01-03 Добавил крышку для парашютного отсека.
2024-01-03 Добавил еще одну потеряшку
2024-01-03 добавил проект бортового кода. засемплировал биг сити лайф
2024-01-04 Добавили массы моделям, теперь они качки как рома
2024-01-04 Добавил в сборку пружины и нить.
2024-01-07 Завершен механизм раскрытия парашюта
2024-01-10 Исправленная модель аппарата
2024-01-20 переделки по плате
2024-01-24 Модель исправлена, сделан габаритный чертёж.
2024-02-01 Переименовал файлы модели.Выгрузил упрощенную модель. Завершил ГЧ
2024-02-01 Забыл добавить две модельки
2024-02-01 Выложил документы на зимнюю сессию в ЛС и сюда
2024-02-01 Плюс презентация
2024-02-02 ПЕРЕДЕЛАЙ ПАЛТЫ
2024-02-03 исправил верхнюю плату
2024-02-03 передвинул пинхеадер и поменял значения резисторов
2024-02-03 чёт сделял
2024-02-03 опять чёт сделял
2024-02-03 Исправили форму печатных плат
2024-02-03 Выгрузили DXF печатных плат
2024-02-07 дбвл бблтк
2024-02-07 поправил контур всех плат
2024-02-07 откатили плату назад
2024-02-09 Почти доделал нижнюю плату
2024-02-09 чипи чипи чапа чапа дуби дуби
2024-02-10 Ошибка повторенная дважды называется - выбор
2024-02-14 пределал плату лидара х6
2024-02-21 Написан парсер пакетов для наземки на RPi
2024-02-21 добавил полигоны на плату и добавил буквы на разъём
2024-02-21 пишем питон и весь код. вячеслав СМААААЙЛ
2024-02-21 Перенес код для RPi наземки
2024-02-21 Пробуем работать с Ctypes для наземки
2024-02-21 Выгружаем бортовой код
2024-02-21 какие-то файлы наземки затерялись
2024-02-21 Перевернул GPS. Теперь надо переразвести
2024-02-23 культивировал плату
2024-02-23 забыли моторчик...
2024-02-24 забыи отладочные пины...
2024-02-24 Проверил плату нижнюю
2024-02-25 Проверил плату верхнюю. Осталось только убрать у GPS отверстие под антенну, чтобы оно не мешало полигону земли
2024-02-29 Наконец-то выгрузил описание проекта плат
2024-02-29 Внес поправки
2024-03-01 Убрал дырку и 100501 раз изменил плату лидара
2024-03-04 Считаем, что платы готовы к производству
2024-03-04 теперь точно готовы
2024-03-04 Сделал заказ плат в Резоните
2024-03-06 Наземка от Ивана
2024-03-08 Добавил пз
2024-03-08 изменил пзпзпзппз
2024-03-10 План-график с марта
2024-03-13 Добавлен график
2024-03-15 Готовим модели для печати
2024-03-15 Создаем макет для сбросов
2024-03-16 графики везде и цифорки добавил
2024-03-16 Добавил кривых на график с ускорением
2024-03-16 мейк ап для мок ап (вроде сделал макет для сбросов)
2024-03-20 Добавил примитивное отображение ориентации
2024-03-20 Добавил нашу упрощённую модель
2024-03-22 Немного оптимизации
2024-03-23 добавлен 3д график лидара
2024-03-23 последняя рабочая версия
2024-03-23 теперь эта последняя
2024-04-19 передал обезьяне все модели аппарата
2024-04-20 переделал плату лидара(((((
2024-04-20 ещё раз(((((((((((((((((((((((((((((((((((((
2024-04-20 ещё и библеотеку скинул
2024-04-24 наземка
2024-04-24 текущее положение дел
2024-04-24 новые держатели линз
2024-04-27 работают датчики, радио.
2024-05-05 этого ни кто не видел
2024-05-08 последняя работающая версия наземки
2024-05-11 тут мало чего поменялось. пережигатель мотор.
2024-05-11 Выгрузили STL файлы для печати
2024-05-11 Обновили модель для спецификации
2024-05-12 Заказана плата лидара v2
2024-06-12 ваня бот
2024-06-15 Последняя версия наземки
